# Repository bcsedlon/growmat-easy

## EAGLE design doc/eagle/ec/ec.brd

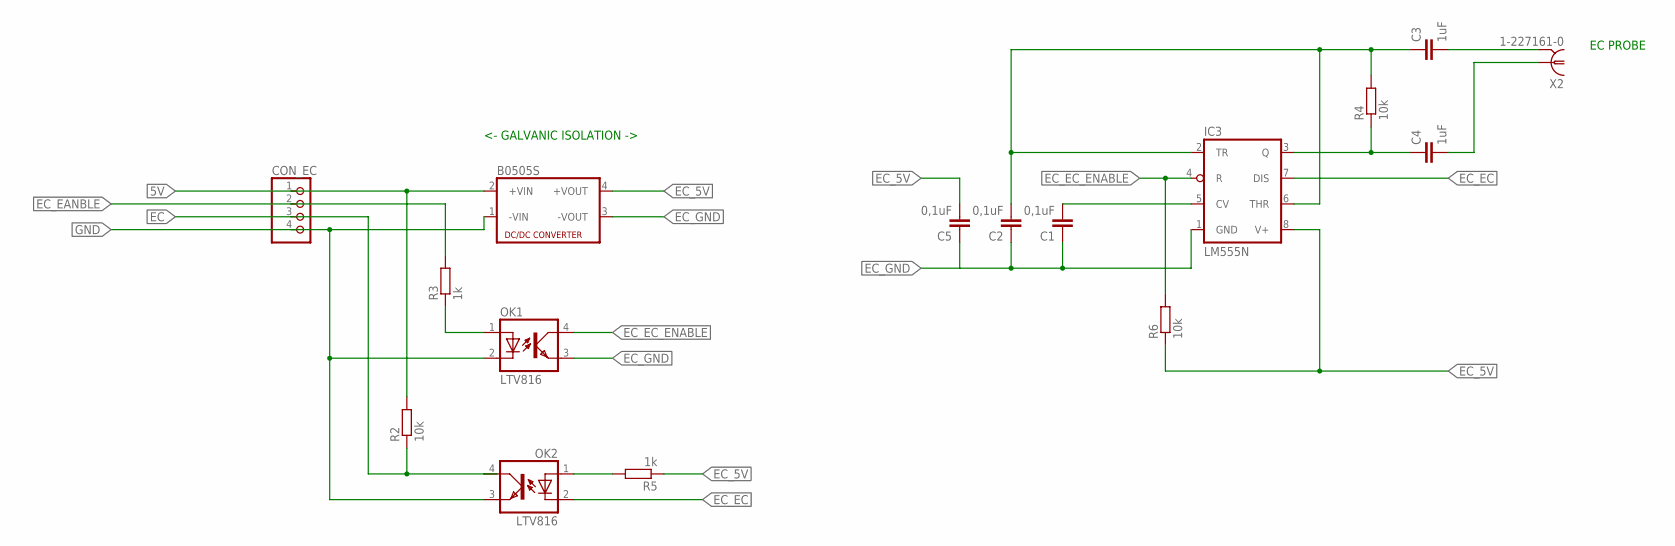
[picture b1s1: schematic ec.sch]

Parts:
B0505S: NME
C1, C2, C5: 0,1uF; C050-024X044
C3, C4: 1uF; C050-024X044
CON_EC: PINHD-1X4; 1X04
IC3: LM555N; DIL08
OK1, OK2: LTV816; DIL04
R2, R4, R6: 10k; 0207/10
R3, R5: 1k; 0207/10
X2: 1-227161-0; AMP_227161

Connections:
5V: B0505S.2 (+VIN), CON_EC.1, R2.2
EC: CON_EC.3, OK2.4 (COL), R2.1
EC_5V: B0505S.4 (+VOUT), C5.2, IC3.8 (V+), R5.1, R6.1
EC_EANBLE: CON_EC.2, R3.2
EC_EC: IC3.7 (DIS), OK2.2 (C)
EC_EC_ENABLE: IC3.4 (R), OK1.4 (COL), R6.2
EC_GND: B0505S.3 (-VOUT), C1.1, C2.1, C5.1, IC3.1 (GND), OK1.3 (EMIT)
GND: B0505S.1 (-VIN), CON_EC.4, OK1.2 (C), OK2.3 (EMIT)
unnamed: C1.2, IC3.5 (CV)
unnamed: C3.2, X2.2
unnamed: C2.2, C3.1, IC3.2 (TR), IC3.6 (THR), R4.2
unnamed: OK1.1 (A), R3.1
unnamed: C4.1, IC3.3 (Q), R4.1
unnamed: OK2.1 (A), R5.2
unnamed: C4.2, X2.1

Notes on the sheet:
EC PROBE
<- GALVANIC ISOLATION ->

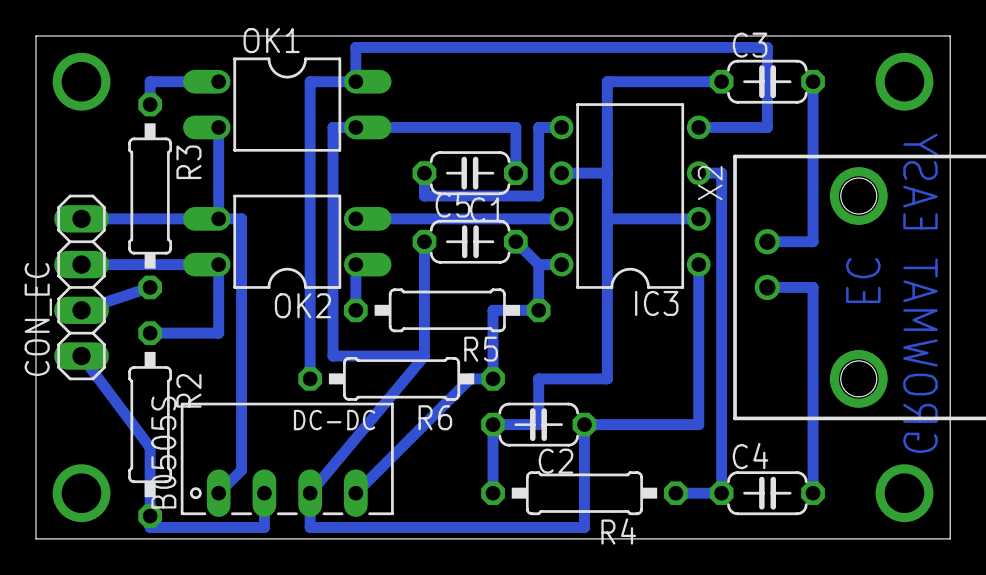
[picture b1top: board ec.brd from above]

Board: 2 copper layers, 50.8 x 27.9 mm, 16 parts (0 on the bottom side), 15 nets.

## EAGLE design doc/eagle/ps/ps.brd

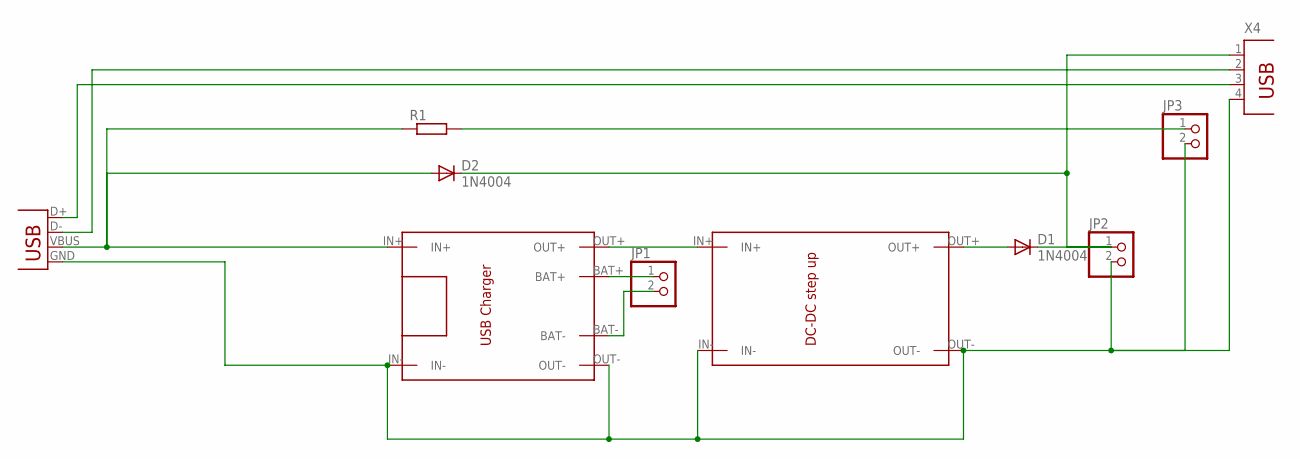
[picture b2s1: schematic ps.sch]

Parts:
D1, D2: 1N4004; DO41-10
JP1, JP2, JP3: PINHD-1X2; 1X02
R1: R-EU_0204/7; 0204/7
U$1: TP4056
U$2: DC-DC_STEPUP
X3: USBPTH; USB-B-PTH
X4: PN87520

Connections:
unnamed: D2.A, R1.1, U$1.IN+, X3.VBUS
unnamed: U$1.OUT+, U$2.IN+
unnamed: JP1.1, U$1.BAT+
unnamed: JP1.2, U$1.BAT-
unnamed: D1.A, U$2.OUT+
unnamed: D1.C, D2.C, JP2.1, X4.1
unnamed: JP2.2, JP3.2, U$1.IN-, U$1.OUT-, U$2.IN-, U$2.OUT-, X3.GND, X4.4
unnamed: JP3.1, R1.2
unnamed: X3.D+, X4.3
unnamed: X3.D-, X4.2

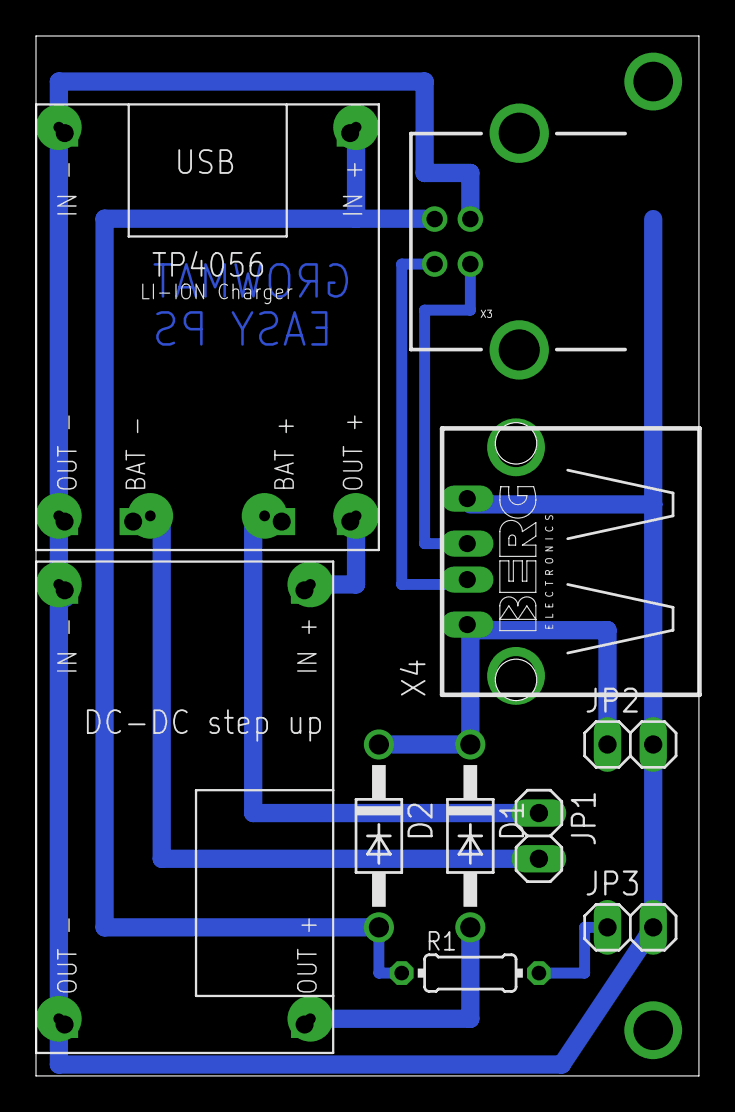
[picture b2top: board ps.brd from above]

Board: 2 copper layers, 36.8 x 57.8 mm, 10 parts (0 on the bottom side), 10 nets.

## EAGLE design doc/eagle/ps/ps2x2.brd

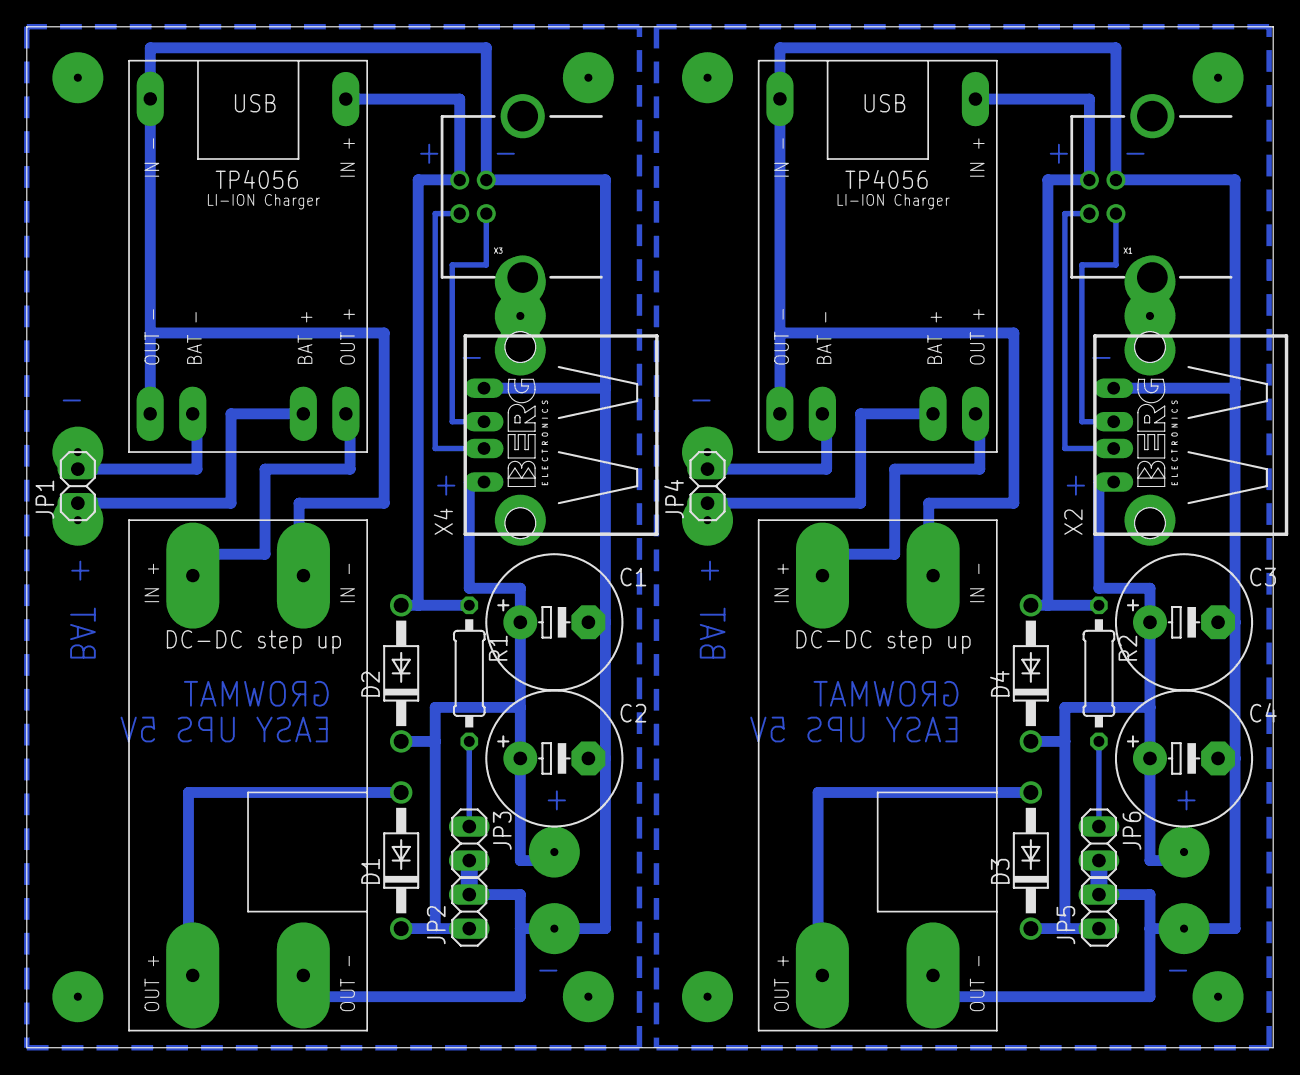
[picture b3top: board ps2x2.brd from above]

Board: 2 copper layers, 93.0 x 76.2 mm, 24 parts (0 on the bottom side), 20 nets.

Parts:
C1, C2, C3, C4: E5-10,5
D1, D2, D3, D4: 1N4004; DO41-10
JP1, JP2, JP3, JP4, JP5, JP6: 1X02
R1, R2: 0207/10
U$1, U$2: TP4056
U$3, U$4: DC-DC_STEPUP
X1, X3: USBPTH; USB-B-PTH
X2, X4: PN87520

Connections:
unnamed: D2.A, R1.1, U$1.IN+, X3.VBUS
unnamed: U$1.OUT+, U$3.IN+
unnamed: C1.-, C2.-, JP2.2, JP3.2, U$1.IN-, U$1.OUT-, U$3.IN-, U$3.OUT-, X3.GND, X4.4
unnamed: JP1.1, U$1.BAT+
unnamed: JP1.2, U$1.BAT-
unnamed: D1.A, U$3.OUT+
unnamed: C1.+, C2.+, D1.C, D2.C, JP2.1, X4.1
unnamed: D4.A, R2.1, U$2.IN+, X1.VBUS
unnamed: U$2.OUT+, U$4.IN+
unnamed: JP3.1, R1.2
unnamed: X3.D+, X4.3
unnamed: X3.D-, X4.2
unnamed: JP4.1, U$2.BAT+
unnamed: JP4.2, U$2.BAT-
unnamed: D3.A, U$4.OUT+
unnamed: C3.+, C4.+, D3.C, D4.C, JP5.1, X2.1
unnamed: JP6.1, R2.2
unnamed: X1.D+, X2.3
unnamed: X1.D-, X2.2
unnamed: C3.-, C4.-, JP5.2, JP6.2, U$2.IN-, U$2.OUT-, U$4.IN-, U$4.OUT-, X1.GND, X2.4

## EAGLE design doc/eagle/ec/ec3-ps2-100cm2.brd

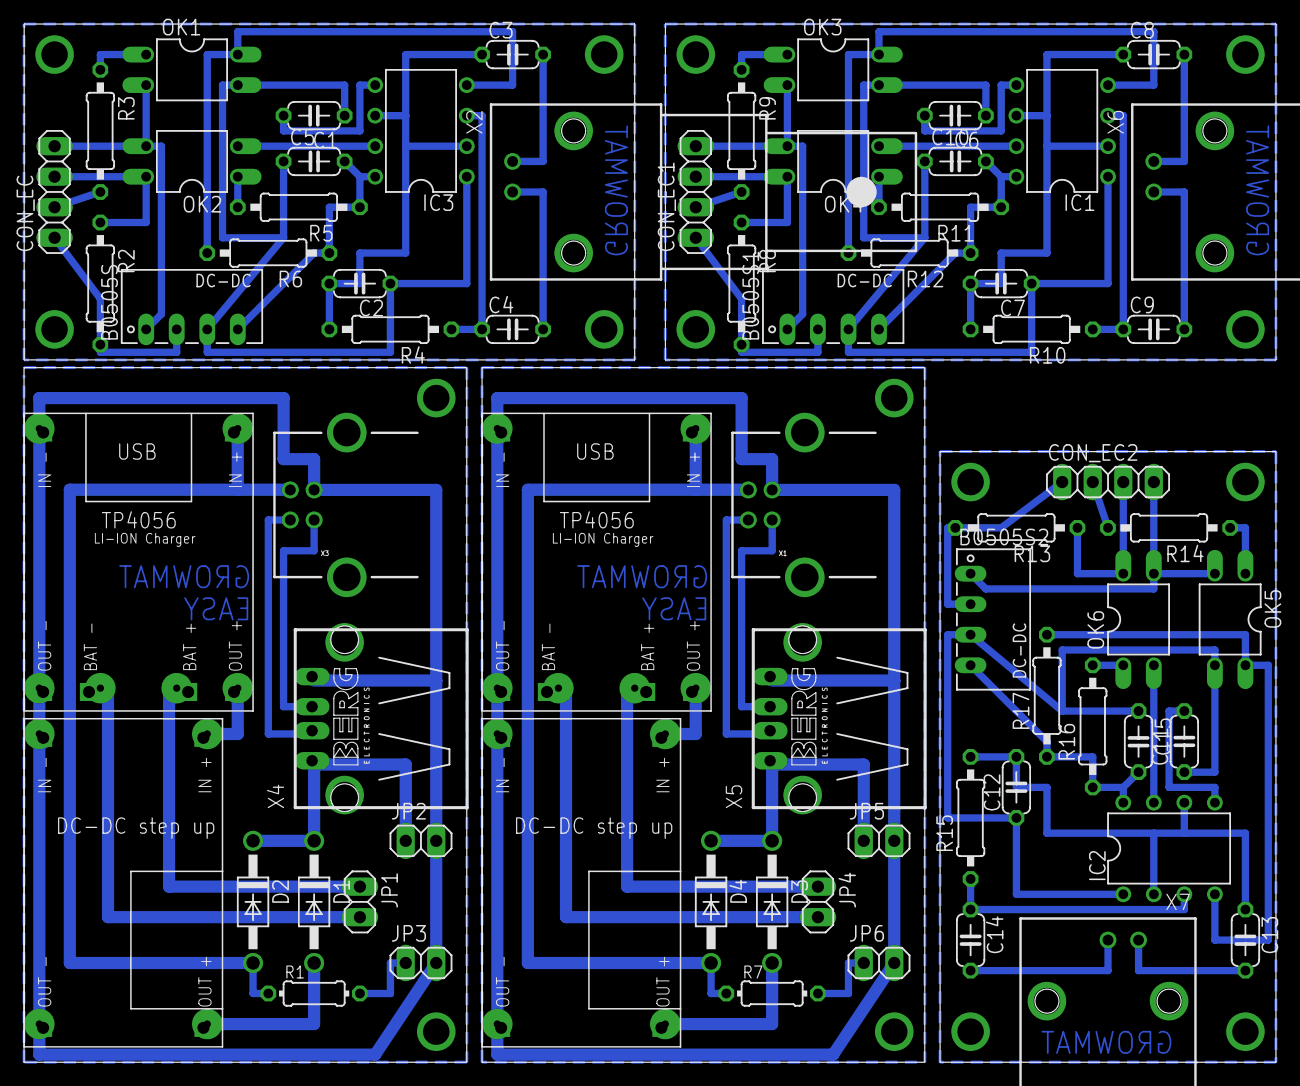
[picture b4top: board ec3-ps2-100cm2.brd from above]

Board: 2 copper layers, 104.1 x 86.4 mm, 68 parts (0 on the bottom side), 65 nets.

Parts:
B0505S, B0505S1, B0505S2: NME
C1, C2, C5, C6, C7, C10, C11, C12, C15: 0,1uF; C050-024X044
C3, C4, C8, C9, C13, C14: 1uF; C050-024X044
CON_EC, CON_EC1, CON_EC2: 1X04
D1, D2, D3, D4: 1N4004; DO41-10
IC1, IC2, IC3: LM555N; DIL08
JP1, JP2, JP3, JP4, JP5, JP6: 1X02
OK1, OK2, OK3, OK4, OK5, OK6: LTV816; DIL04
R1, R7: 0204/7
R2, R4, R6, R8, R10, R12, R13, R15, R17: 10k; 0207/10
R3, R5, R9, R11, R14, R16: 1k; 0207/10
U$1, U$3: TP4056
U$2, U$4: DC-DC_STEPUP
X1, X3: USBPTH; USB-B-PTH
X2, X6, X7: 1-227161-0; AMP_227161
X4, X5: PN87520

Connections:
5V: B0505S.2, CON_EC.1, R2.2
5V1: B0505S1.2, CON_EC1.1, R8.2
5V2: B0505S2.2, CON_EC2.1, R13.2
EC: CON_EC.3, OK2.4, R2.1
EC1: CON_EC1.3, OK4.4, R8.1
EC2: CON_EC2.3, OK6.4, R13.1
EC_5V: B0505S.4, C5.2, IC3.8, R5.1, R6.1
EC_5V1: B0505S1.4, C10.2, IC1.8, R11.1, R12.1
EC_5V2: B0505S2.4, C15.2, IC2.8, R16.1, R17.1
EC_EANBLE: CON_EC.2, R3.2
EC_EANBLE1: CON_EC1.2, R9.2
EC_EANBLE2: CON_EC2.2, R14.2
EC_EC: IC3.7, OK2.2
EC_EC1: IC1.7, OK4.2
EC_EC2: IC2.7, OK6.2
EC_EC_ENABLE: IC3.4, OK1.4, R6.2
EC_EC_ENABLE1: IC1.4, OK3.4, R12.2
EC_EC_ENABLE2: IC2.4, OK5.4, R17.2
EC_GND: B0505S.3, C1.1, C2.1, C5.1, IC3.1, OK1.3
EC_GND1: B0505S1.3, C6.1, C7.1, C10.1, IC1.1, OK3.3
EC_GND2: B0505S2.3, C11.1, C12.1, C15.1, IC2.1, OK5.3
GND: B0505S.1, CON_EC.4, OK1.2, OK2.3
GND1: B0505S1.1, CON_EC1.4, OK3.2, OK4.3
GND2: B0505S2.1, CON_EC2.4, OK5.2, OK6.3
unnamed: D2.A, R1.1, U$1.IN+, X3.VBUS
unnamed: U$1.OUT+, U$2.IN+
unnamed: JP2.2, JP3.2, U$1.IN-, U$1.OUT-, U$2.IN-, U$2.OUT-, X3.GND, X4.4
unnamed: JP1.1, U$1.BAT+
unnamed: JP1.2, U$1.BAT-
unnamed: D1.A, U$2.OUT+
unnamed: D1.C, D2.C, JP2.1, X4.1
unnamed: C1.2, IC3.5
unnamed: D4.A, R7.1, U$3.IN+, X1.VBUS
unnamed: JP3.1, R1.2
unnamed: X3.D+, X4.3
unnamed: X3.D-, X4.2
unnamed: U$3.OUT+, U$4.IN+
unnamed: JP4.1, U$3.BAT+
unnamed: JP4.2, U$3.BAT-
unnamed: D3.A, U$4.OUT+
unnamed: D3.C, D4.C, JP5.1, X5.1
unnamed: JP6.1, R7.2
unnamed: X1.D+, X5.3
unnamed: X1.D-, X5.2
unnamed: JP5.2, JP6.2, U$3.IN-, U$3.OUT-, U$4.IN-, U$4.OUT-, X1.GND, X5.4
unnamed: OK3.1, R9.1
unnamed: C6.2, IC1.5
unnamed: C7.2, C8.1, IC1.2, IC1.6, R10.2
unnamed: C3.2, X2.2
unnamed: C2.2, C3.1, IC3.2, IC3.6, R4.2
unnamed: OK1.1, R3.1
unnamed: C4.1, IC3.3, R4.1
unnamed: OK2.1, R5.2
unnamed: C4.2, X2.1
unnamed: C9.1, IC1.3, R10.1
unnamed: OK4.1, R11.2
unnamed: C8.2, X6.2
unnamed: C9.2, X6.1
unnamed: OK5.1, R14.1
unnamed: C11.2, IC2.5
unnamed: C12.2, C13.1, IC2.2, IC2.6, R15.2
unnamed: C14.1, IC2.3, R15.1
unnamed: OK6.1, R16.2
unnamed: C13.2, X7.2
unnamed: C14.2, X7.1

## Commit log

2016-10-03 alarms fix
2016-10-04 add quick control add alarm off event
2016-10-04 alarm message count fix
2016-10-05 class Alarm keypad pause
2016-10-05 fix leaflet/growmat-easy-leaflet.svg
2016-10-05 remove debug Serial.print
2016-10-09 last version developed in Arduino 1.6.12
2016-10-09 initial commit in eclipse with arduino plugin
2016-10-09 add set clock, send sms
2016-10-10 reorganized code be aware of free memory in next work
2016-10-11 info sms
2016-10-11 fix info sms
2016-10-12 fix ui
2016-10-16 demo_1 output pin control
2016-10-16 fix vent temp default
2016-10-21 add manual and English folder
2016-10-22 add external alarm, rename vent to fan
2016-10-22 add eclipse config files for PRAN computer
2016-10-22 add hw drawings
2016-10-24 save controlMode from SMS, add PCB
2016-10-24 add hex file
2016-10-26 add English leaflet /growmat_easy-leaflet-blue-A6-en.svg
2016-11-06 add banner, pcb rev2
2016-11-20 cannafest 2016, nano
2016-11-23 growmat easy hydro - add ph
2016-11-28 add radio control MCE07
2016-11-28 fix rf cmd, add rf sniffer
2016-12-07 add DS18B20 temp sensor, cmd from serial
2016-12-12 add eagle schema
2016-12-14 eagle files
2016-12-14 add level measurement
2016-12-15 variables rename
2016-12-16 clean code
2017-01-06 add python api
2017-01-24 add power source 2 (eagle)
2017-02-02 mirror fixes
2017-02-04 add wifi esp8266
2017-02-06 lcd text edit
2017-02-08 ecenable
2017-02-09 fix level
2017-06-15 change i2c keypad addr, 1+A reset display, change light alarms delay, watchdog test
2017-06-15 remove alarms from not __HYDRO__
2017-08-09 sn 0001 / 0002, fix (night) temperature
